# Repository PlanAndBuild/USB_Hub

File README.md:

<div align="center">
  
</div>

---

<h1 align="center">Just HUB</h1>

<p align="center">
 <small><I>It is Just Hub.<I></small>
</p>

<p align="center">
  <b>Just HUB is very simple 4 port USB hub based on the GL852G chip.</b>
  <br>
  <b>It is designed for Hackclub fallout, because I needed few more hours to fly out to Shenzhen! </b>
  </br>
</p>

## Features

**4x USB-A ports**

**Just one USB-C cable gives out 4 USB-A ports**

**and thats all because IT IS JUST HUB lol**

---
## Why I designed it?
I needed just few more hours to get the ticket for Fallout and I thinked what could I do, something simple and not very time consuming. Firstly I've had an idea to built ligthning strike detector wit GNSS for precise time mesuring but it would take a little bit too much time, so I asked on slack, what could I built and they told me to make usb hub or tamagotchi. So i choosed hub because its useful.

---
## How to build it:
 - You just buy all of the components and PCBs
 - Solder everything in place
 - Print enclosure
 - Put board into the enclousre and just tigthen the screw
 - And then just plug it in and id sholud work! 
---
## Zine

<div align="center">
  
</div>

## Images

<div align="center">

</div>

## ⚖️ License

This project is licensed under the **Creative Commons Attribution-NonCommercial-ShareAlike 4.0 International (CC BY-NC-SA 4.0)** License.

[![CC BY-NC-SA 4.0][cc-by-nc-sa-shield]][cc-by-nc-sa]

You are free to share and adapt this material under the following terms:
* **Attribution** — You must give appropriate credit to the original author.
* **NonCommercial** — You may not use the material for commercial purposes.
* **ShareAlike** — If you remix, transform, or build upon the material, you must distribute your contributions under the same license.

[cc-by-nc-sa]: http://creativecommons.org/licenses/by-nc-sa/4.0/
[cc-by-nc-sa-shield]: https://img.shields.io/badge/License-CC%20BY--NC--SA%204.0-lightgrey.svg

## BOM

| Item No. | Qty. | Value | MPN (Part Number) | LCSC | Datasheet | Unit Price ($) | Total Price ($) |
| --- | --- | --- | --- | --- | --- | --- | --- |
| 1 | 5 | `1uF` | CL10A105KO8NNNC | [C1592](https://www.lcsc.com/product-detail/C1592.html) | [PDF](https://www.lcsc.com/datasheet/C1592.pdf) | 0.0124 | 0.0620 |
| 2 | 8 | `100nF` | CL10B104KO8NNNC | [C66501](https://www.lcsc.com/product-detail/C66501.html) | [PDF](https://www.lcsc.com/datasheet/C66501.pdf) | 0.0073 | 0.0584 |
| 3 | 1 | `10uF` | RVT1H100M0505 | [C72487](https://www.lcsc.com/product-detail/C72487.html) | [PDF](https://www.lcsc.com/datasheet/C72487.pdf) | 0.0284 | 0.0284 |
| 4 | 2 | `20pF` | TCC0603COG200J101CT | [C880611](https://www.lcsc.com/product-detail/C880611.html) | [PDF](https://www.lcsc.com/datasheet/C880611.pdf) | 0.0034 | 0.0068 |
| 5 | 4 | `100uF` | RVT1V101M0607 | [C72478](https://www.lcsc.com/product-detail/C72478.html) | [PDF](https://www.lcsc.com/datasheet/C72478.pdf) | 0.0304 | 0.1216 |
| 6 | 1 | `LED` | XL-2012SURC | [C965812](https://www.lcsc.com/product-detail/C965812.html) | [PDF](https://www.lcsc.com/datasheet/C965812.pdf) | 0.0070 | 0.0070 |
| 7 | 1 | `35V2A` | F06F2TH | [C41398700](https://www.lcsc.com/product-detail/C41398700.html) | [PDF](https://www.lcsc.com/datasheet/C41398700.pdf) | 0.0314 | 0.0314 |
| 8 | 6 | `600ohm/100mhz` | SCBG160808U601T | [C480860](https://www.lcsc.com/product-detail/C480860.html) | - | 0.0042 | 0.0252 |
| 9 | 1 | `USB_C_Receptacle_USB2.0_16P` | TYPE-C 16PIN 2MD(073) | [C2765186](https://www.lcsc.com/product-detail/C2765186.html) | [PDF](https://www.lcsc.com/datasheet/C2765186.pdf) | 0.0707 | 0.0707 |
| 10 | 4 | `USB_A` | AF 90 WJDG | [C456018](https://www.lcsc.com/product-detail/C456018.html) | [PDF](https://www.lcsc.com/datasheet/C456018.pdf) | 0.0485 | 0.1940 |
| 11 | 2 | `680R` | GR0603F680RT5G00 | [C49653123](https://www.lcsc.com/product-detail/C49653123.html) | [PDF](https://www.lcsc.com/datasheet/C49653123.pdf) | 0.0012 | 0.0024 |
| 12 | 1 | `100k` | FRC0603F1003TS | [C2906980](https://www.lcsc.com/product-detail/C2906980.html) | [PDF](https://www.lcsc.com/datasheet/C2906980.pdf) | 0.0019 | 0.0019 |
| 13 | 2 | `30k` | 0603WAF3002T5E | [C22984](https://www.lcsc.com/product-detail/C22984.html) | [PDF](https://www.lcsc.com/datasheet/C22984.pdf) | 0.0018 | 0.0036 |
| 14 | 2 | `5.1k` | 1RC0603F5101 | [C53224208](https://www.lcsc.com/product-detail/C53224208.html) | [PDF](https://www.lcsc.com/datasheet/C53224208.pdf) | 0.0014 | 0.0028 |
| 15 | 1 | `10k` | CR0603JA0103G | [C101254](https://www.lcsc.com/product-detail/C101254.html) | [PDF](https://www.lcsc.com/datasheet/C101254.pdf) | 0.0016 | 0.0016 |
| 16 | 1 | `47k` | CL0603JN47KP | [C46635305](https://www.lcsc.com/product-detail/C46635305.html) | [PDF](https://www.lcsc.com/datasheet/C46635305.pdf) | 0.0011 | 0.0011 |
| 17 | 1 | `AMS1117-3.3` | AMS1117-3.3OF | [C50313802](https://www.lcsc.com/product-detail/C50313802.html) | [PDF](https://www.lcsc.com/datasheet/C50313802.pdf) | 0.0338 | 0.0338 |
| 18 | 1 | `GL852G-OHY60_C7501404` | GL852G-OHY60 | [C7501404](https://www.lcsc.com/product-detail/C7501404.html) | [PDF](https://www.lcsc.com/datasheet/C7501404.pdf) | 1.0751 | 1.0751 |
| 19 | 1 | `12MHz` | K3A120002010 | [C368730](https://www.lcsc.com/product-detail/C368730.html) | [PDF](https://www.lcsc.com/datasheet/C368730.pdf) | 0.0580 | 0.0580 |
| 20 | 1 | `PCB` | - | - | - | 2.0000 | 2.0000 |
| 21 | 1 | `3D Printing` | - | - | - | Free | 0.0000 |
| 22 | 4 | `M3x12mm screws` | - | - | - | - | 0.0782 |
| **Total** |  |  |  |  |  |  | **$$3.8640** |

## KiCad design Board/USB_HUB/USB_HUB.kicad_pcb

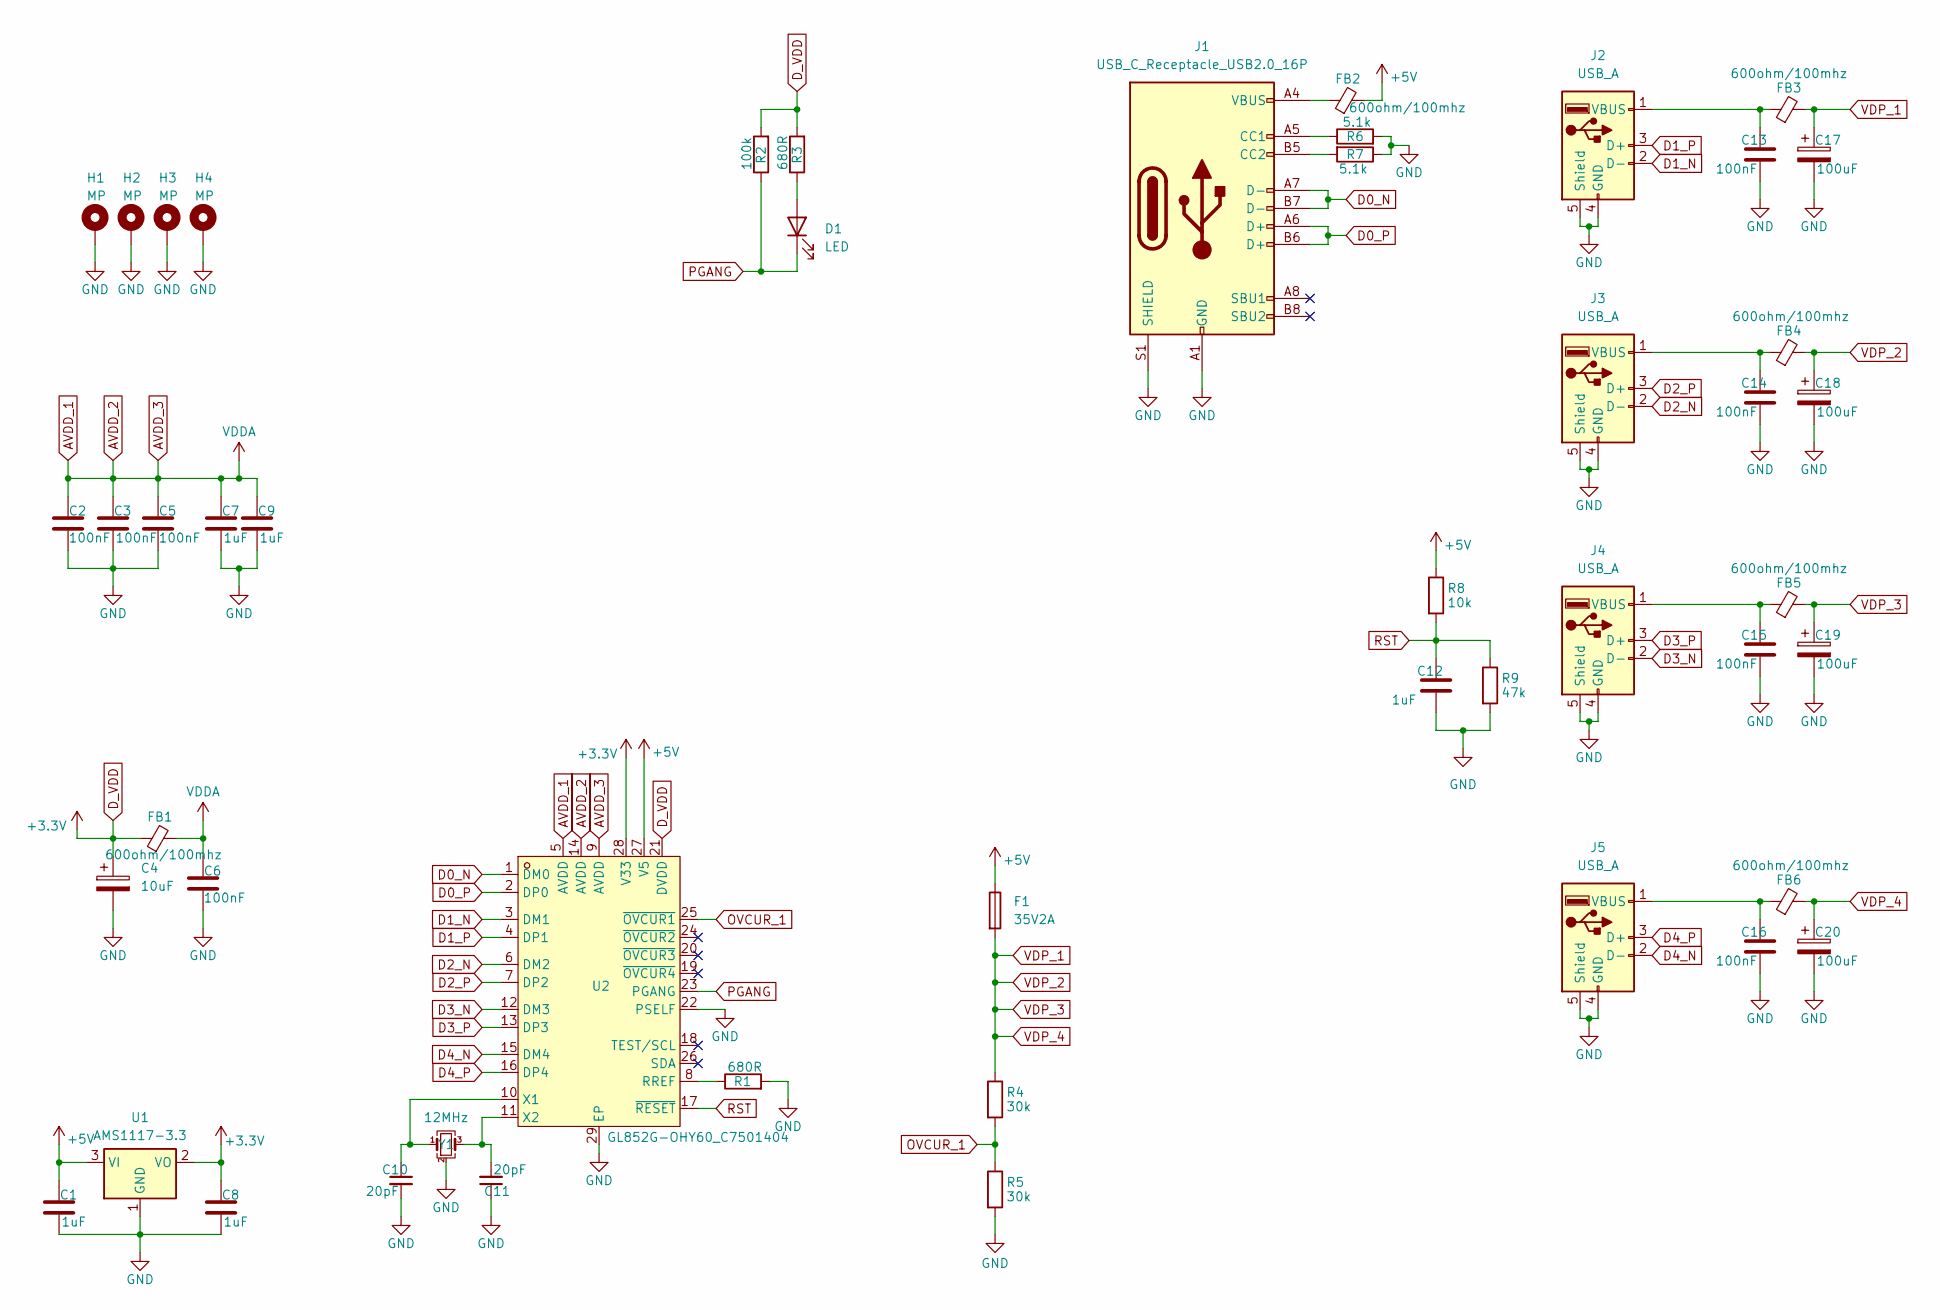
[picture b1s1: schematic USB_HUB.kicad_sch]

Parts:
C1, C7, C8, C9, C12: 1uF; C_0603_1608Metric; MPN CL10A105KO8NNNC; LCSC C1592
C2, C3, C5, C6, C13, C14, C15, C16: 100nF; C_0603_1608Metric; MPN CL10B104KO8NNNC; LCSC C66501
C4: 10uF; CP_Elec_5x5.4; MPN RVT1H100M0505; LCSC C72487
C10, C11: 20pF; C_0603_1608Metric; MPN TCC0603COG200J101CT; LCSC C880611
C17, C18, C19, C20: 100uF; CP_Elec_6.3x7.7; MPN RVT1V101M0607; LCSC C72478
D1: LED; D_0805_2012Metric; MPN XL-2012SURC; LCSC C965812
F1: 35V2A; Fuse_0603_1608Metric; MPN F06F2TH; LCSC C41398700
FB1, FB2, FB3, FB4, FB5, FB6: 600ohm/100mhz; L_0603_1608Metric; MPN SCBG160808U601T; LCSC C480860
H1, H2, H3, H4: MP; MountingHole_3.2mm_M3_Pad_Via
J1: USB_C_Receptacle_USB2.0_16P; USB_C_Receptacle_Palconn_UTC16-G; MPN TYPE-C 16PIN 2MD(073); LCSC C2765186
J2, J3, J4, J5: USB_A; USB_A_Kycon_KUSBX-AS1N-B_Horizontal; MPN AF 90 WJDG; LCSC C456018
R1, R3: 680R; R_0603_1608Metric; MPN GR0603F680RT5G00; LCSC C49653123
R2: 100k; R_0603_1608Metric; MPN FRC0603F1003TS; LCSC C2906980
R4, R5: 30k; R_0603_1608Metric; MPN 0603WAF3002T5E; LCSC C22984
R6, R7: 5.1k; R_0603_1608Metric; MPN 1RC0603F5101; LCSC C53224208
R8: 10k; R_0603_1608Metric; MPN CR0603JA0103G; LCSC C101254
R9: 47k; R_0603_1608Metric; MPN CL0603JN47KP; LCSC C46635305
U1: AMS1117-3.3; SOT-89-3
U2: GL852G-OHY60_C7501404; QFN-28_L5.0-W5.0-P0.50-BL-EP; MPN GL852G-OHY60; LCSC Part C7501404
Y1: 12MHz; Crystal_SMD_3225-4Pin_3.2x2.5mm; MPN K3A120002010; LCSC C368730

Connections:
+5V: C1.1, F1.1, FB2.2, R8.1, U1.3 (VI), U2.27 (V5)
AVDD_1: C2.1, C3.1, C5.1, C6.1, C7.1, C9.1, FB1.2, U2.5 (AVDD), U2.9 (AVDD), U2.14 (AVDD)
D0_N: J1.A7 (D-), J1.B7 (D-), U2.1 (DM0)
D0_P: J1.A6 (D+), J1.B6 (D+), U2.2 (DP0)
D1_N: J2.2 (D-), U2.3 (DM1)
D1_P: J2.3 (D+), U2.4 (DP1)
D2_N: J3.2 (D-), U2.6 (DM2)
D2_P: J3.3 (D+), U2.7 (DP2)
D3_N: J4.2 (D-), U2.12 (DM3)
D3_P: J4.3 (D+), U2.13 (DP3)
D4_N: J5.2 (D-), U2.15 (DM4)
D4_P: J5.3 (D+), U2.16 (DP4)
D_VDD: C4.1, C8.1, FB1.1, R2.2, R3.2, U1.2 (VO), U2.21 (DVDD), U2.28 (V33)
GND: C1.2, C2.2, C3.2, C4.2, C5.2, C6.2, C7.2, C8.2, C9.2, C10.2, C11.1, C12.2, C13.2, C14.2, C15.2, C16.2, C17.2, C18.2, C19.2, C20.2, H1.1 (1_1), H2.1 (1_1), H3.1 (1_1), H4.1 (1_1), J1.A1 (GND), J1.A12 (GND), J1.B1 (GND), J1.B12 (GND), J1.S1 (SHIELD), J2.4 (GND), J2.5 (Shield), J3.4 (GND), J3.5 (Shield), J4.4 (GND), J4.5 (Shield), J5.4 (GND), J5.5 (Shield), R1.2, R5.2, R6.2, R7.1, R9.2, U1.1 (GND), U2.22 (PSELF), U2.29 (EP), Y1.2 (G), Y1.4 (G)
unnamed: D1.2 (A), R3.1
unnamed: FB2.1, J1.A4 (VBUS), J1.A9 (VBUS), J1.B4 (VBUS), J1.B9 (VBUS)
unnamed: J1.A5 (CC1), R6.1
unnamed: J1.B5 (CC2), R7.2
unnamed: C13.1, FB3.1, J2.1 (VBUS)
unnamed: C14.1, FB4.1, J3.1 (VBUS)
unnamed: C15.1, FB5.1, J4.1 (VBUS)
unnamed: C16.1, FB6.1, J5.1 (VBUS)
unnamed: R1.1, U2.8 (RREF)
unnamed: C10.1, U2.10 (X1), Y1.1
unnamed: C11.2, U2.11 (X2), Y1.3
OVCUR_1: R4.2, R5.1, U2.25 (~OVCUR1)
PGANG: D1.1 (K), R2.1, U2.23 (PGANG)
RST: C12.1, R8.2, R9.1, U2.17 (~RESET)
VDP_1: C17.1, C18.1, C19.1, C20.1, F1.2, FB3.2, FB4.2, FB5.2, FB6.2, R4.1

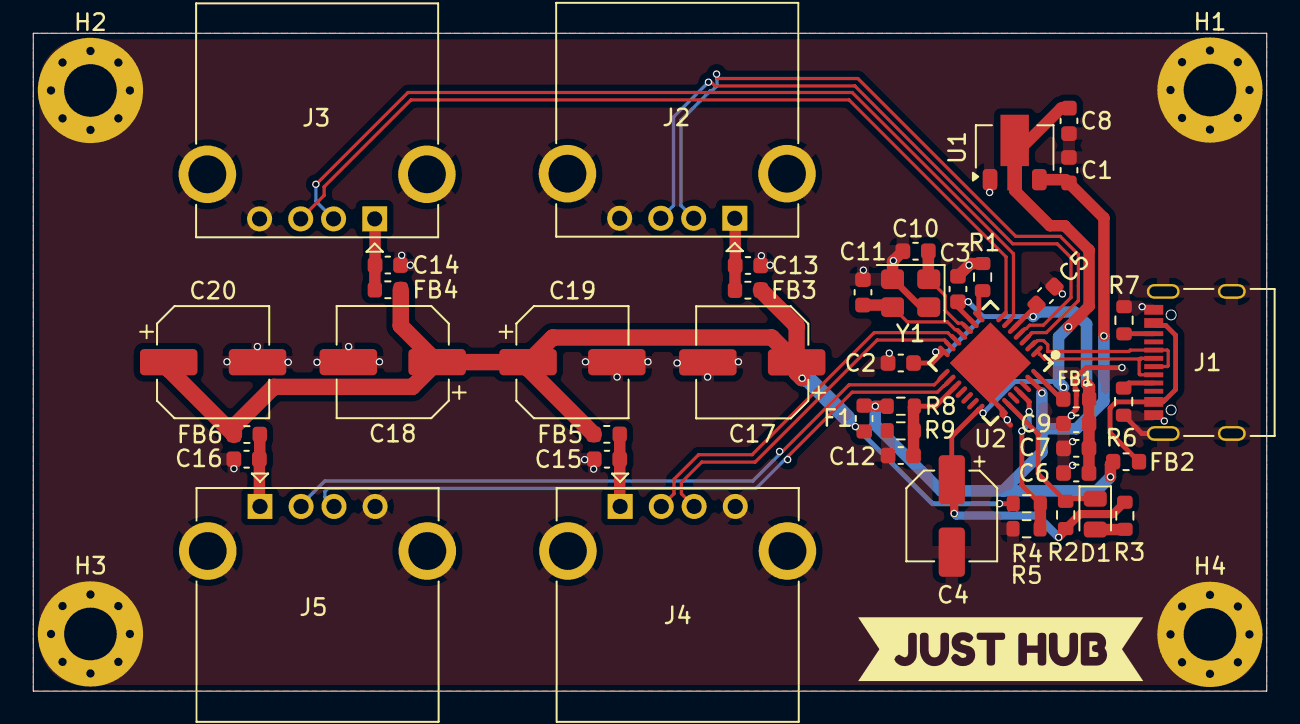
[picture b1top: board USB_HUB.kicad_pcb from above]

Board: 2 copper layers, 75.0 x 40.0 mm, 51 parts (1 on the bottom side), 29 nets.

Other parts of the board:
kibuzzard-6A37130F: G***; kibuzzard-6A37130F
kibuzzard-6A371354: G***; kibuzzard-6A371354

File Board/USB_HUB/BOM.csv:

"Reference","Qty","Value","DNP","Exclude from BOM","Exclude from Board","Footprint","Datasheet","MPN","LCSC"
"C1,C7,C8,C9,C12","5","1uF","","","","Capacitor_SMD:C_0603_1608Metric","https://www.lcsc.com/datasheet/C1592.pdf","CL10A105KO8NNNC","C1592"
"C2,C3,C5,C6,C13,C14,C15,C16","8","100nF","","","","Capacitor_SMD:C_0603_1608Metric","https://www.lcsc.com/datasheet/C66501.pdf","CL10B104KO8NNNC","C66501"
"C4","1","10uF","","","","Capacitor_SMD:CP_Elec_5x5.4","https://www.lcsc.com/datasheet/C72487.pdf","RVT1H100M0505","C72487"
"C10,C11","2","20pF","","","","Capacitor_SMD:C_0603_1608Metric","https://www.lcsc.com/datasheet/C880611.pdf","TCC0603COG200J101CT","C880611"
"C17,C18,C19,C20","4","100uF","","","","Capacitor_SMD:CP_Elec_6.3x7.7","https://www.lcsc.com/datasheet/C72478.pdf","RVT1V101M0607","C72478"
"D1","1","LED","","","","Diode_SMD:D_0805_2012Metric","https://www.lcsc.com/datasheet/C965812.pdf","XL-2012SURC","C965812"
"F1","1","35V2A","","","","Fuse:Fuse_0603_1608Metric","https://www.lcsc.com/datasheet/C41398700.pdf","F06F2TH","C41398700"
"FB1,FB2,FB3,FB4,FB5,FB6","6","600ohm/100mhz","","","","Inductor_SMD:L_0603_1608Metric","-","SCBG160808U601T","C480860"
"J1","1","USB_C_Receptacle_USB2.0_16P","","","","Connector_USB:USB_C_Receptacle_Palconn_UTC16-G","https://www.lcsc.com/datasheet/C2765186.pdf","TYPE-C 16PIN 2MD(073)","C2765186"
"J2,J3,J4,J5","4","USB_A","","","","Connector_USB:USB_A_Kycon_KUSBX-AS1N-B_Horizontal","https://www.lcsc.com/datasheet/C456018.pdf","AF 90 WJDG","C456018"
"R1,R3","2","680R","","","","Resistor_SMD:R_0603_1608Metric","https://www.lcsc.com/datasheet/C49653123.pdf","GR0603F680RT5G00","C49653123"
"R2","1","100k","","","","Resistor_SMD:R_0603_1608Metric","https://www.lcsc.com/datasheet/C2906980.pdf","FRC0603F1003TS","C2906980"
"R4,R5","2","30k","","","","Resistor_SMD:R_0603_1608Metric","https://www.lcsc.com/datasheet/C22984.pdf","0603WAF3002T5E","C22984"
"R6,R7","2","5.1k","","","","Resistor_SMD:R_0603_1608Metric","https://www.lcsc.com/datasheet/C53224208.pdf","1RC0603F5101","C53224208"
"R8","1","10k","","","","Resistor_SMD:R_0603_1608Metric","https://www.lcsc.com/datasheet/C101254.pdf","CR0603JA0103G","C101254"
"R9","1","47k","","","","Resistor_SMD:R_0603_1608Metric","https://www.lcsc.com/datasheet/C46635305.pdf","CL0603JN47KP","C46635305"
"U1","1","AMS1117-3.3","","","","Package_TO_SOT_SMD:SOT-89-3","http://www.advanced-monolithic.com/pdf/ds1117.pdf","",""
"U2","1","GL852G-OHY60_C7501404","","","","EasyEDA:QFN-28_L5.0-W5.0-P0.50-BL-EP","https://www.lcsc.com/datasheet/C7501404.pdf","GL852G-OHY60","C7501404"
"Y1","1","12MHz","","","","Crystal:Crystal_SMD_3225-4Pin_3.2x2.5mm","https://www.lcsc.com/datasheet/C368730.pdf","K3A120002010","C368730"

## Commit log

2026-06-21 Readme
2026-06-21 added board
    added board, BOM, readme, renders
2026-06-21 Add images section to README
    Added images section with PCB renders to README.
2026-06-21 Models and PCB
2026-06-21 images
2026-06-24 Add BOM section to README
    Added a Bill of Materials (BOM) section with item details.
2026-06-24 Enhance BOM table with pricing information
    Added unit price and total price columns to BOM table.
2026-06-24 BOM csv
2026-06-24 Add build instructions to README
    Added a section on how to build the project, including steps for assembly and setup.
2026-06-25 Update BOM.csv with specific screw details
2026-06-25 Update component details in README.md
    Updated the component list in the README to reflect the correct part number for AMS1117-3.3 and changed the description for M3 screws.
2026-06-25 Fix U1 datasheet link in BOM.csv
    Updated the datasheet link for U1 in BOM.
2026-06-26 Document design motivation in README
    Added a section explaining the design motivation for the project.
